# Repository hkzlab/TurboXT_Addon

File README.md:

# Turbo / Reset addon board for the IBM XT (5160)

## Introduction

This board is originally based on schematics I found floating around on VCFED, and adds the following to an IBM XT:

- Switchable clock between **standard** (4.77Mhz) and **turbo** (8Mhz if the oscillator installed on the board is 24Mhz)
- Auto disable of turbo-mode during DMA
- Reset button header

### Disclaimer

I take NO responsibility for what happens if you decide to build and use this card. Your computer might crash, catch fire or be destroyed in other nasty ways.
Also, as this card is mostly based on the work of others, You're encourauged to take what you deem fit from this, and use it in your projects!

## Installation

The board is installed on the 8284 socket (near the 8088 processor) via turned pin headers, and the 8284 is placed on a socket on top of the board.
Usually, an additional socket is added to the bottom headers to gain some vertical spacing, as part of the board sits above 8088 and 8087 sockets.

The TurboXT then has 4 additional labeled connections to make on the motherboard via wire.

### DMA

These connections are required to automatically disable turbo during DMA:

- HRQDMA from pin 10 of the 8237 DMA controller (U28) or pin 5 of U57 (74LS20)
- DMAWAIT from pin 7 of a 74LS175 flipflop (U88)

Note that these two connections actually end up feeding into the same NAND gate, you can mix them up and no issue will arise.

### Power

These are optional but highly recommended to provide an additional source of power beside the 8284 socket:

- VCC: Connect to a +5V spot on the board
- GND: Connect to a GND spot on the board

There are many connection points you can use (VCC/GND legs of another IC for example), but along the side of the XT power connector
there are two empty resistor footprints on my board that were perfect for the connection.

**Check continuity with a multimeter!!!**

# Known issues and caveats 

- The original 8088 is rated 5Mhz. Replace it with at least an 8Mhz rated variant.
- The board sits on top of (but should not make contact with) the 8088 and 8087. These can get hot, add a fan or something to keep them cooler.
- Some CMOS variants of the 8284 do not drive the OSC signal when the F/C pin is high. This is required for this board to work. I tested mine with the original Intel 8284.
- The components on top of the board could cause some clearance issues with cards installed in slot 8. Some redesigning is required to address this.
- You can try other oscillators in place of the 24Mhz one. Remember that the resulting frequency will be divided by 3.

## Bill of Materials

- C1:	10uF/25v electrolitic cap
- C2-9: 8x 100nF ceramic caps
- R1, R2, R4: 3x 10k resistors
- R3: 470ohm resistors
- U2: 74LS92
- U3: 74LS74
- U4: 74LS02
- U5: 74LS00
- U7: 74HCT14
- X1: 24Mhz oscillator (The board divides this frequency by 3)
- 18pin socket for 8284
- 18pin turned header strip
- 18pin socket as a spacer between motherboard and addon
- Snapped pin headers for connectors on the board

# Credits

Original schematics from [this](www.vcfed.org/forum/showthread.php?70923-IBM-5160-overclock-Sergey%92s-way) thread on VCFED.

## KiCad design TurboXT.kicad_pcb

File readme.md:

# Installation

- HRQDMA from pin 10 of the 8237 DMA controller (U28)
- DMAWAIT from pin 7 of a 74LS175 flipflop (U88)

# Credits

Original schematics from [this](www.vcfed.org/forum/showthread.php?70923-IBM-5160-overclock-Sergey%92s-way) thread on VCFED.

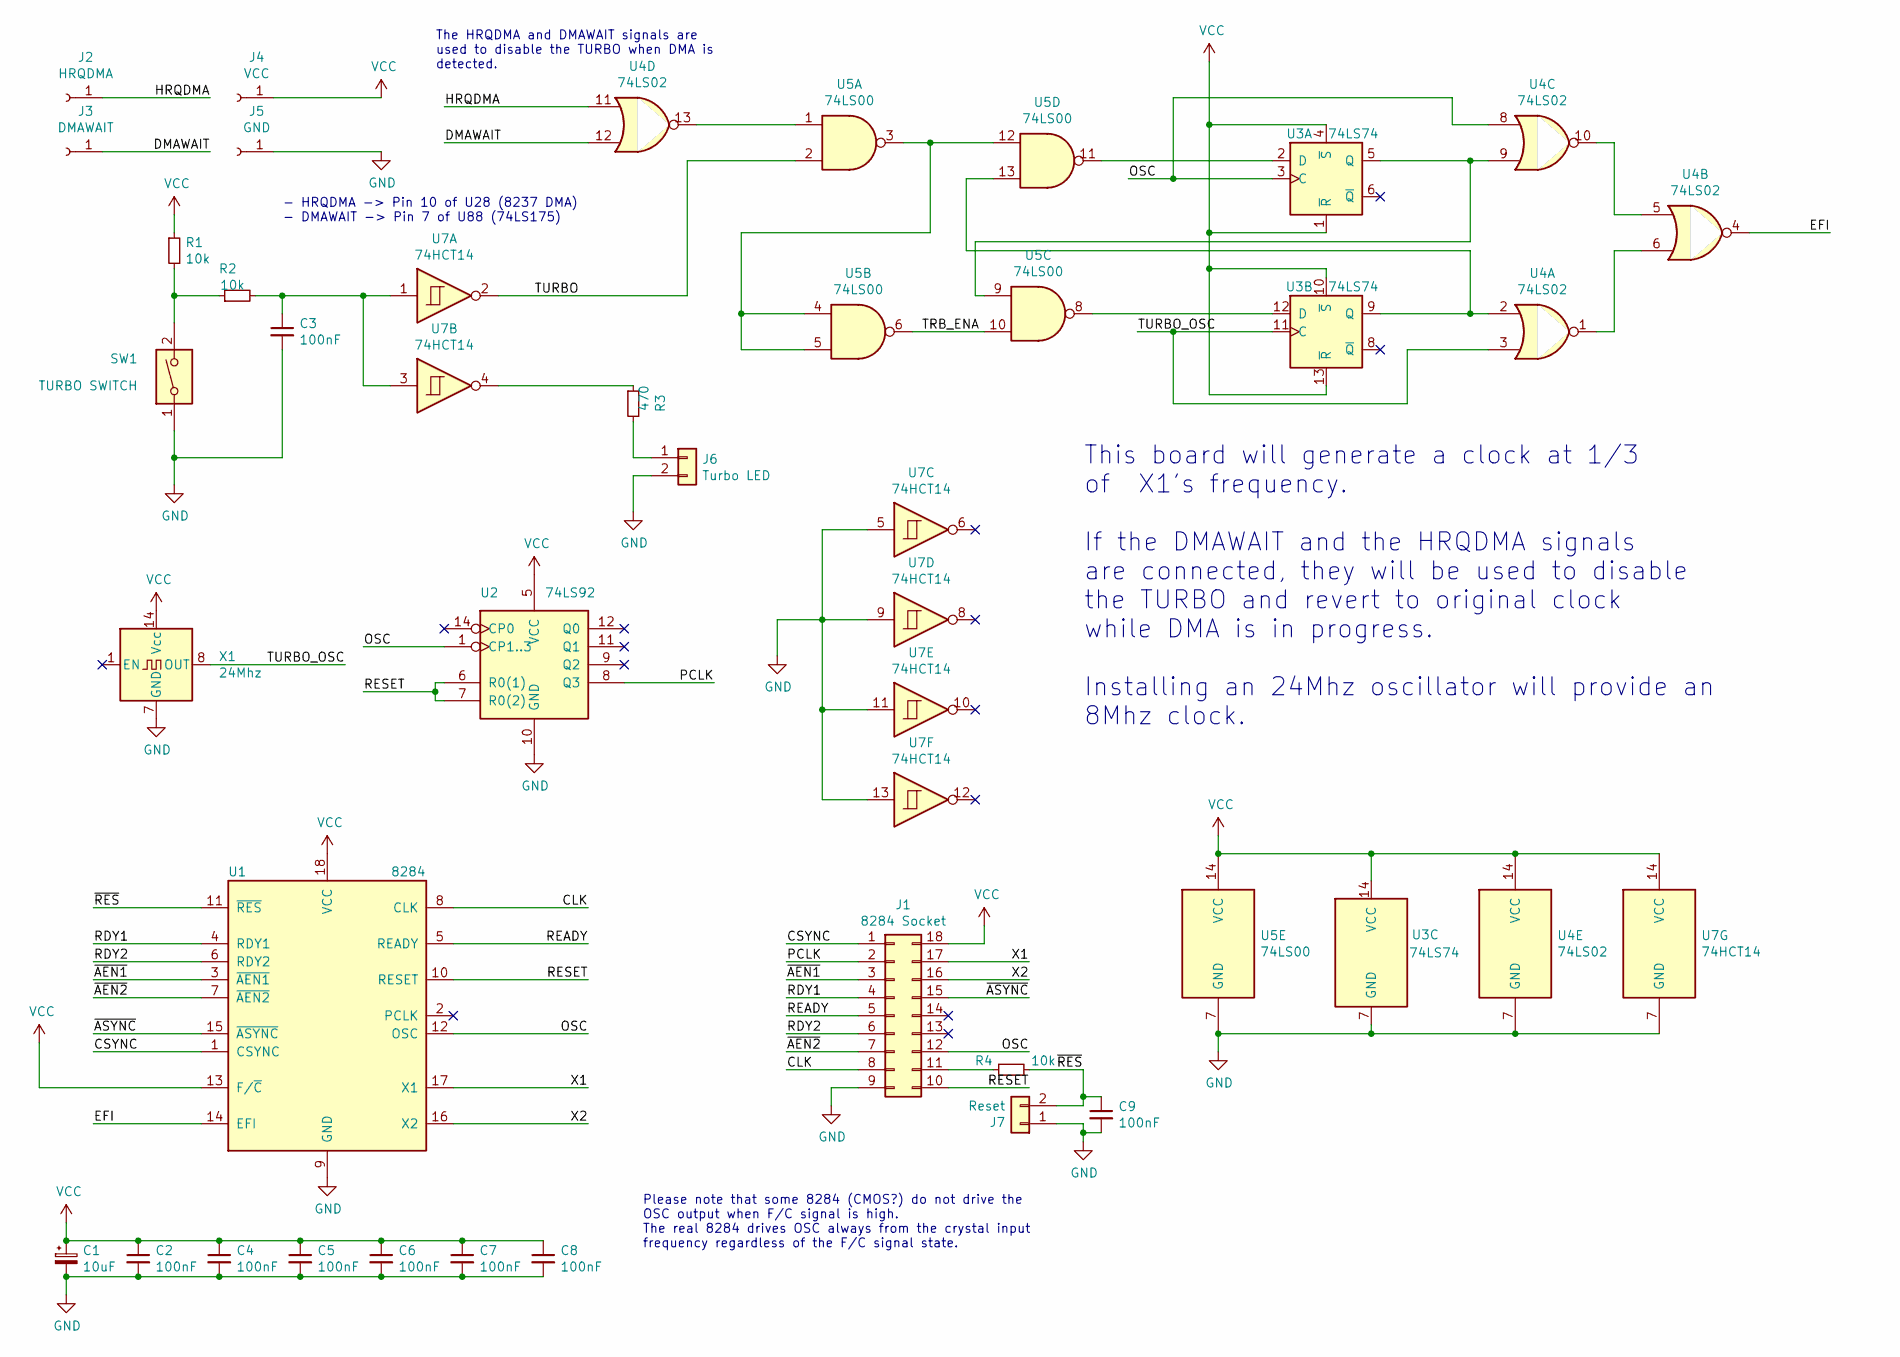
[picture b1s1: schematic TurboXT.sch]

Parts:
C1: 10uF; CP_Radial_D5.0mm_P2.50mm
C2, C3, C4, C5, C6, C7, C8, C9: 100nF; C_Disc_D6.0mm_W2.5mm_P5.00mm
J1: 8284 Socket; DIP-18_W7.62mm_LongPads
J2: HRQDMA; Pin_D1.0mm_L10.0mm
J3: DMAWAIT; Pin_D1.0mm_L10.0mm
J4: VCC; Pin_D1.0mm_L10.0mm
J5: GND; Pin_D1.0mm_L10.0mm
J6: Turbo LED; PinHeader_1x02_P2.54mm_Vertical
J7: Reset; PinHeader_1x02_P2.54mm_Vertical
R1, R2, R4: 10k; R_Axial_DIN0207_L6.3mm_D2.5mm_P10.16mm_Horizontal
R3: 470; R_Axial_DIN0207_L6.3mm_D2.5mm_P10.16mm_Horizontal
SW1: TURBO SWITCH; PinHeader_1x02_P2.54mm_Vertical
U1: 8284; DIP-18_W7.62mm_Socket_LongPads
U2: 74LS92; DIP-14_W7.62mm_LongPads
U3: 74LS74; DIP-14_W7.62mm_LongPads
U4: 74LS02; DIP-14_W7.62mm_LongPads
U5: 74LS00; DIP-14_W7.62mm_LongPads
U7: 74HCT14; DIP-14_W7.62mm_LongPads
X1: 24Mhz; Oscillator_DIP-14-8

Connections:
/CLK: J1.8, U1.8 (CLK)
/CSYNC: J1.1, U1.1 (CSYNC)
/DMAWAIT: J3.1, U4.12
/EFI: U1.14 (EFI), U4.4
/HRQDMA: J2.1, U4.11
/OSC: J1.12, U1.12 (OSC), U2.1 (CP1..3), U3.3 (C), U4.8
/PCLK: J1.2, U2.8 (Q3)
/RDY1: J1.4, U1.4 (RDY1)
/RDY2: J1.6, U1.6 (RDY2)
/READY: J1.5, U1.5 (READY)
/RESET: J1.10, U1.10 (RESET), U2.6 (R0(1)), U2.7 (R0(2))
/TRB_ENA: U5.6, U5.10
/TURBO: U5.2, U7.2
/TURBO_OSC: U3.11 (C), U4.3, X1.8 (OUT)
/X1: J1.17, U1.17 (X1)
/X2: J1.16, U1.16 (X2)
/~AEN1: J1.3, U1.3 (~AEN1~)
/~AEN2: J1.7, U1.7 (~AEN2~)
/~ASYNC: J1.15, U1.15 (~ASYNC~)
/~RES: C9.1, J7.2, R4.2, U1.11 (~RES~)
GND: C1.2, C2.2, C3.2, C4.2, C5.2, C6.2, C7.2, C8.2, C9.2, J1.9, J5.1, J6.2, J7.1, SW1.1, U1.9 (GND), U2.10 (GND), U3.7 (GND), U4.7 (GND), U5.7 (GND), U7.5, U7.7 (GND), U7.9, U7.11, U7.13, X1.7 (GND)
unnamed: C3.1, R2.2, U7.1, U7.3
unnamed: J1.11, R4.1
unnamed: J6.1, R3.2
unnamed: R1.2, R2.1, SW1.2
unnamed: R3.1, U7.4
unnamed: U3.2 (D), U5.11
unnamed: U3.5 (Q), U4.9, U5.9
unnamed: U3.9 (Q), U4.2, U5.13
unnamed: U3.12 (D), U5.8
unnamed: U4.1, U4.6
unnamed: U4.5, U4.10
unnamed: U4.13, U5.1
unnamed: U5.3, U5.4, U5.5, U5.12
VCC: C1.1, C2.1, C4.1, C5.1, C6.1, C7.1, C8.1, J1.18, J4.1, R1.1, U1.13 (F/~C~), U1.18 (VCC), U2.5 (VCC), U3.1 (~R), U3.4 (~S), U3.10 (~S), U3.13 (~R), U3.14 (VCC), U4.14 (VCC), U5.14 (VCC), U7.14 (VCC), X1.14 (Vcc)

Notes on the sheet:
The HRQDMA and DMAWAIT signals are used to disable the TURBO when DMA is detected.
This board will generate a clock at 1/3 of X1's frequency. If the DMAWAIT and the HRQDMA signals are connected, they will be used to disable the TURBO and revert to original clock while DMA is in progress. Installing an 24Mhz oscillator will provide an 8Mhz clock.
- HRQDMA -> Pin 10 of U28 (8237 DMA) - DMAWAIT -> Pin 7 of U88 (74LS175)
Please note that some 8284 (CMOS?) do not drive the OSC output when F/C signal is high. The real 8284 drives OSC always from the crystal input frequency regardless of the F/C signal state.

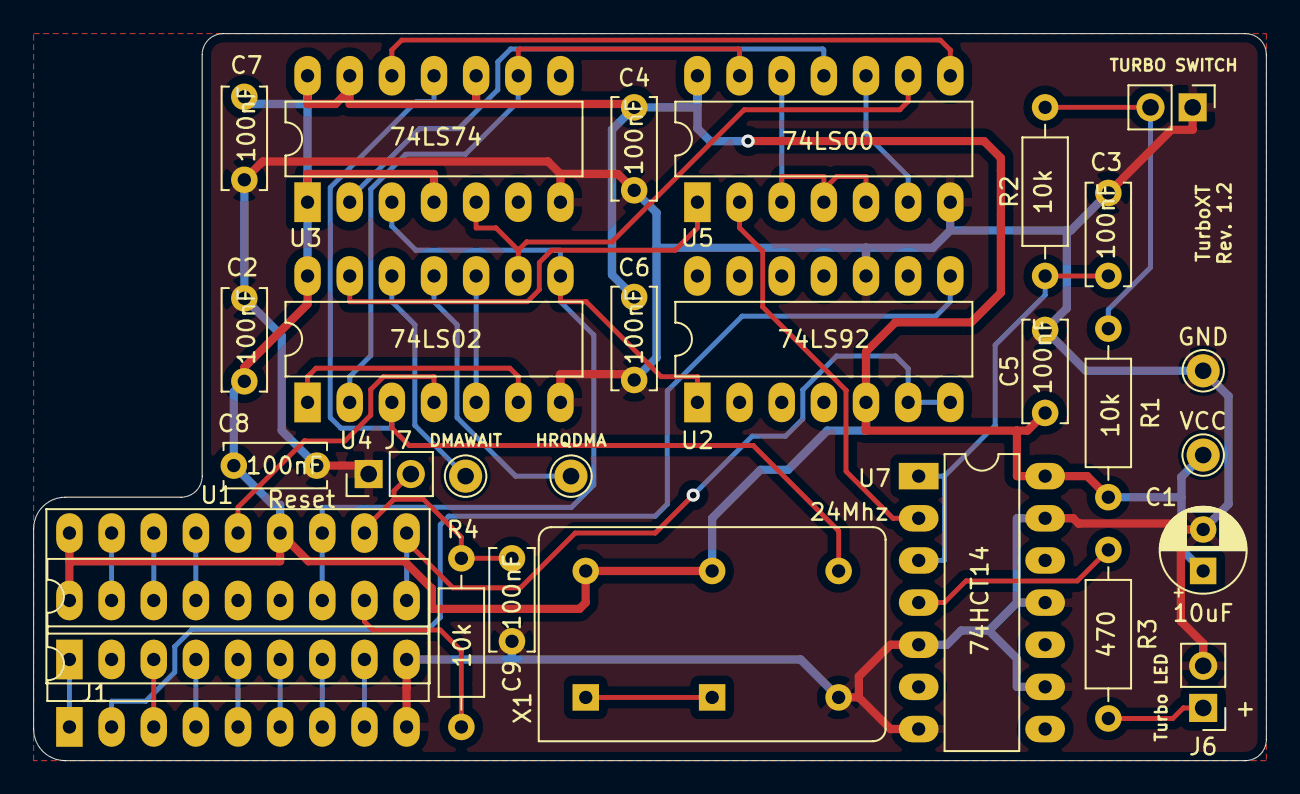
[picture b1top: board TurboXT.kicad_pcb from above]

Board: 2 copper layers, 74.3 x 43.8 mm, 28 parts (0 on the bottom side), 35 nets.

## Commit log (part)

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2021-03-08 TurboXT addon schematic
2021-03-08 Drawn the schematic
2021-03-08 Gerbers + silkscreen
2021-03-08 Change connection for led
2021-03-08 Fix schematics
2021-05-21 Renamed notes into readme
2021-05-21 Add credits
2021-05-21 Add notes to PCB and changed silkscreen
2021-05-21 More notes in schematics
2021-05-22 Add original schematics
2021-05-22 Add old schematics
2021-05-22 Add notes
2021-05-28 Connect reset of 74LS92
2021-05-28 Fixed double README
2021-05-28 Change led value and silkscreen
2021-05-28 Updated silkscreen
2021-05-28 Add reset button
2021-05-28 Move silkscreen a bit
2021-05-28 Add cap for deboucing
2021-05-29 Start writing the README
2021-05-29 Additional note to the README
2024-05-20 Begin implementing address decoding

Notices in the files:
TurboXT.sch:
Copyright (c) 2014 Sergey Kiselev
Modified (c) 2019 Inmbolmie
Modified (c) 2021 Hkz
